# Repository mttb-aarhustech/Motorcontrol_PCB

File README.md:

# Motorcontrol_PCB
Motorcontrol PCB AARHUS TECH

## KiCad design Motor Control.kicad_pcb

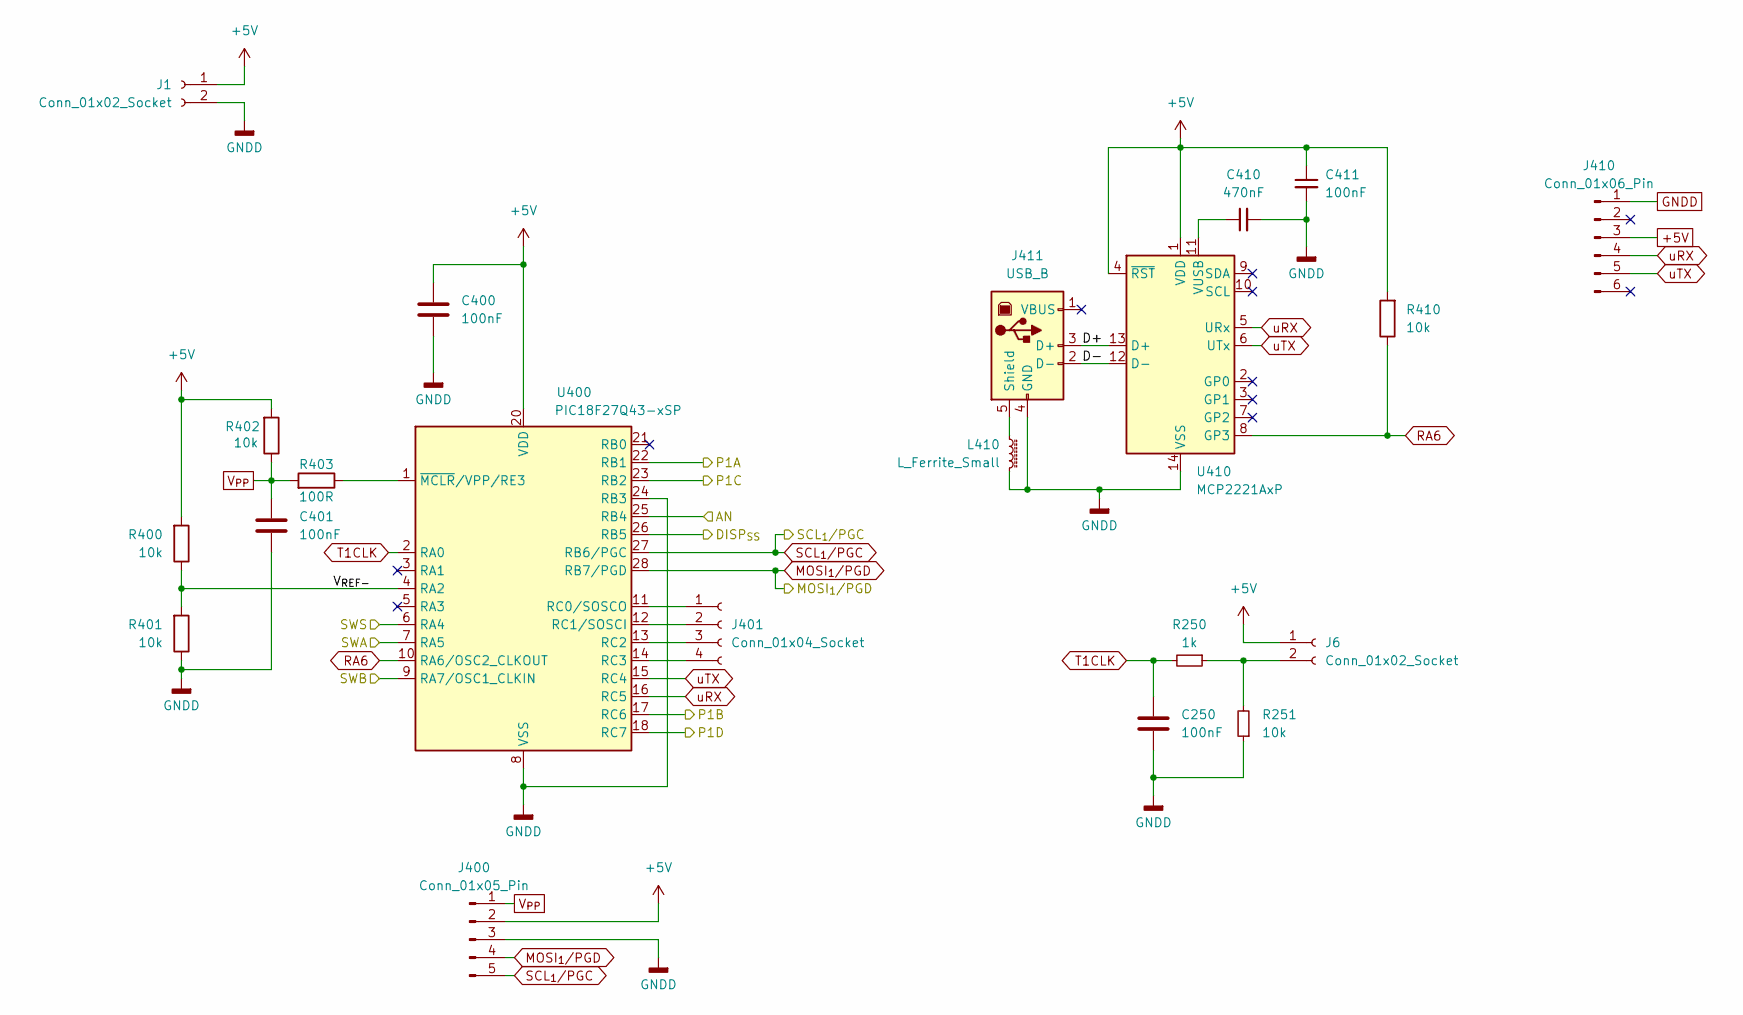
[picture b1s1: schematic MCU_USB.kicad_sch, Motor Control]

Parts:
C250, C400, C401, C411: 100nF; C_Rect_L7.2mm_W2.5mm_P5.00mm_FKS2_FKP2_MKS2_MKP2; Part number 135-8304
C410: 470nF; C_Rect_L7.2mm_W2.5mm_P5.00mm_FKS2_FKP2_MKS2_MKP2; Part number 172-5820
J1, J6: Conn_01x02_Socket; PhoenixContact_MCV_1,5_2-G-5.08_1x02_P5.08mm_Vertical
J400: Conn_01x05_Pin; PinSocket_1x05_P2.54mm_Horizontal; Part number 233-9362
J401: Conn_01x04_Socket; PinSocket_1x04_P2.54mm_Horizontal
J410: Conn_01x06_Pin; PinSocket_1x06_P2.54mm_Vertical
J411: USB_B; USB_B_TE_5787834_Vertical; Part number 1076666
L410: L_Ferrite_Small; R_Axial_DIN0411_L9.9mm_D3.6mm_P12.70mm_Horizontal; Part number 467-3315
R250: 1k; R_Axial_DIN0207_L6.3mm_D2.5mm_P10.16mm_Horizontal; Part number 05.000.0410
R251, R400, R401, R402, R410: 10k; R_Axial_DIN0207_L6.3mm_D2.5mm_P10.16mm_Horizontal; Part number 05.000.0510
R403: 100R; R_Axial_DIN0207_L6.3mm_D2.5mm_P10.16mm_Horizontal; Part number 05.000.0510
U400: PIC18F27Q43-xSP; DIP-28_W7.62mm_Socket_LongPads
U410: MCP2221AxP; DIP-14_W7.62mm_Socket_LongPads; Part number 171-7757

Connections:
+5V: C400.1, C411.1, J1.1, J6.1, J400.2, J410.3, R400.2, R402.2, R410.2, U400.20 (VDD), U410.1 (VDD), U410.4 (~RST); also elsewhere on the board
/Disp & encoder/DISP_{SS}: U400.26 (RB5); also elsewhere on the board
/Disp & encoder/SWA: U400.7 (RA5); also elsewhere on the board
/Disp & encoder/SWB: U400.9 (RA7/OSC1_CLKIN); also elsewhere on the board
/Disp & encoder/SWS: U400.6 (RA4); also elsewhere on the board
/H Bridge/P1A: U400.22 (RB1); also elsewhere on the board
/H Bridge/P1B: U400.17 (RC6); also elsewhere on the board
/H Bridge/P1C: U400.23 (RB2); also elsewhere on the board
/H Bridge/P1D: U400.18 (RC7); also elsewhere on the board
/MCU & USB/AN: U400.25 (RB4); also elsewhere on the board
/MCU & USB/D+: J411.3 (D+), U410.13 (D+)
/MCU & USB/D-: J411.2 (D-), U410.12 (D-)
/MCU & USB/V_{REF-}: R400.1, R401.2, U400.4 (RA2)
GNDD: C250.2, C400.2, C401.2, C410.2, C411.2, J1.2, J400.3, J410.1, J411.4 (GND), L410.2, R251.1, R401.1, U400.8 (VSS), U400.19 (VSS), U400.24 (RB3), U410.14 (VSS); also elsewhere on the board
MOSI_{1}/PGD: J400.4, U400.28 (RB7/PGD); also elsewhere on the board
unnamed: J6.2, R250.1, R251.2
unnamed: J401.1, U400.11 (RC0/SOSCO)
unnamed: J401.2, U400.12 (RC1/SOSCI)
unnamed: J401.3, U400.13 (RC2)
unnamed: J401.4, U400.14 (RC3)
unnamed: J411.5 (Shield), L410.1
unnamed: R403.1, U400.1 (~MCLR/VPP/RE3)
unnamed: C410.1, U410.11 (VUSB)
RA6: R410.1, U400.10 (RA6/OSC2_CLKOUT), U410.8 (GP3)
SCL_{1}/PGC: J400.5, U400.27 (RB6/PGC); also elsewhere on the board
T1CLK: C250.1, R250.2, U400.2 (RA0)
V_{PP}: C401.1, J400.1, R402.1, R403.2
uRX: J410.4, U400.16 (RC5), U410.5 (URx)
uTX: J410.5, U400.15 (RC4), U410.6 (UTx)

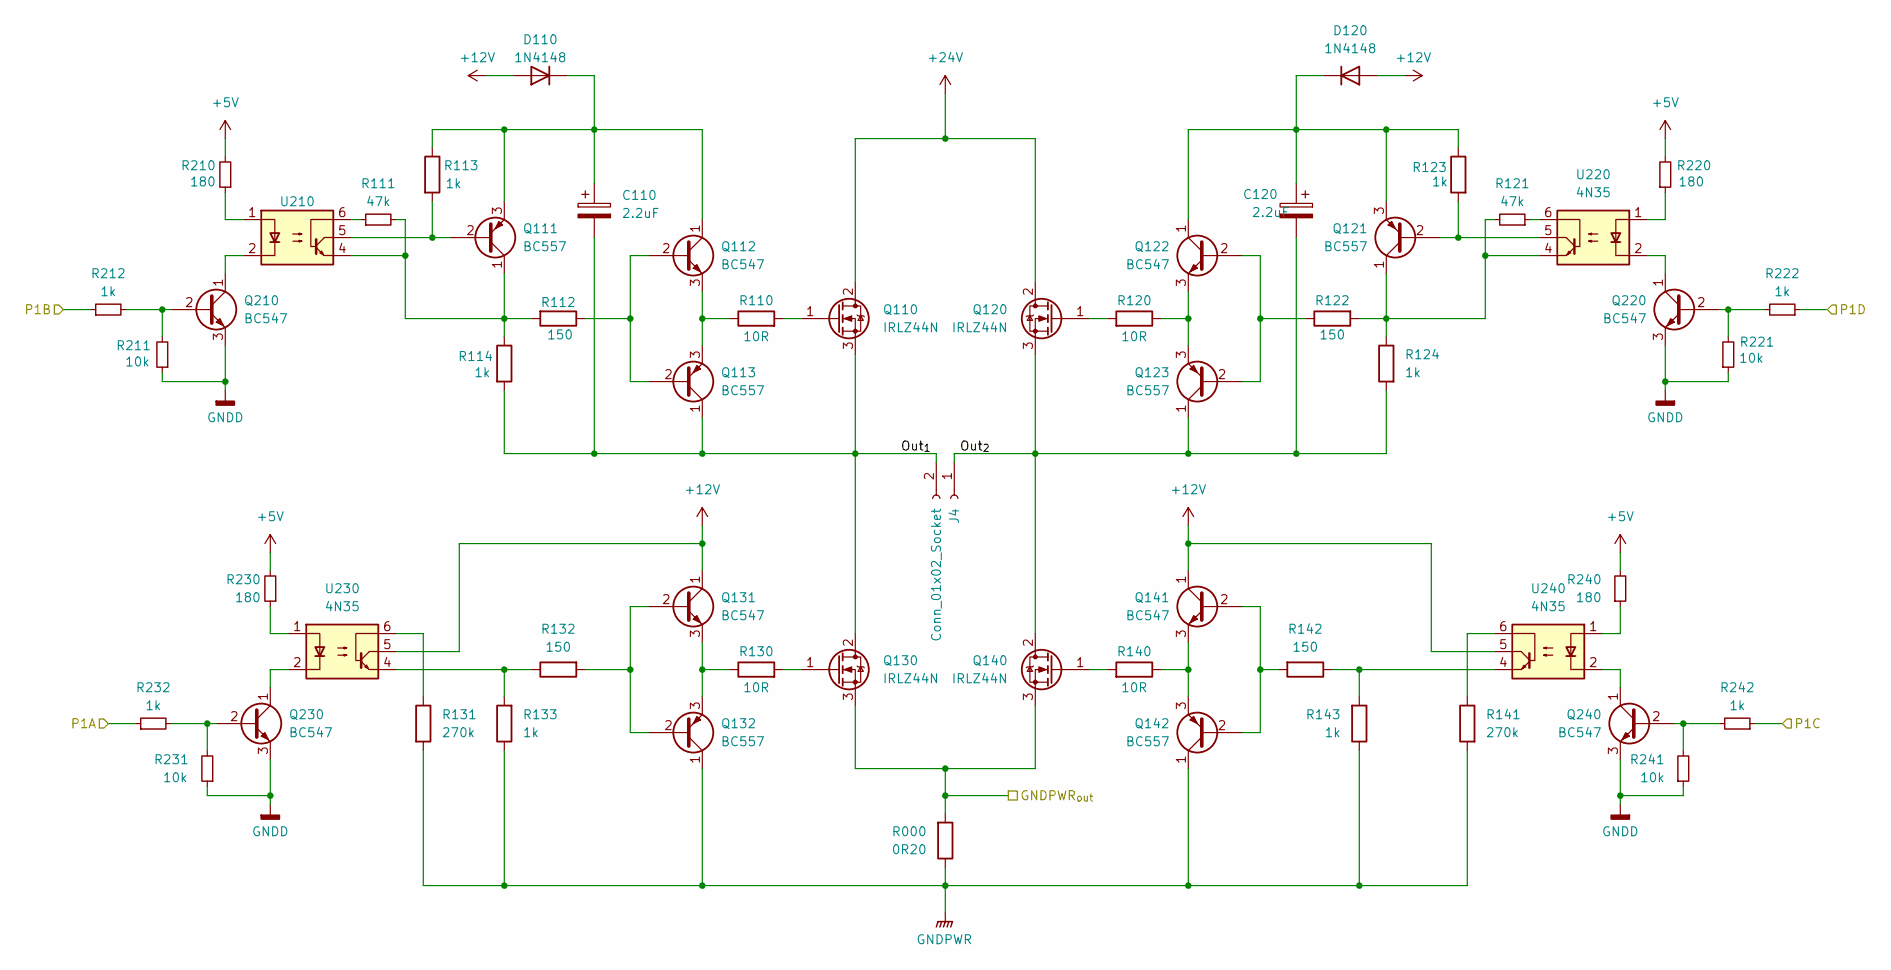
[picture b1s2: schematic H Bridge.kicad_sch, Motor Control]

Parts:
C110, C120: 2.2uF; CP_Radial_D4.0mm_P2.00mm; Part number 8766797
D110, D120: 1N4148; D_DO-35_SOD27_P7.62mm_Horizontal; Part number 00.001.4148
J4: Conn_01x02_Socket; PhoenixContact_MCV_1,5_2-G-5.08_1x02_P5.08mm_Vertical
Q110, Q120, Q130, Q140: IRLZ44N; TO-220-3_Horizontal_TabDown_HoleToCenter; Part number 8651418
Q111, Q113, Q121, Q123, Q132, Q142: BC557; TO-92_Inline_Wide; Part number 01.020.0557
Q112, Q122, Q131, Q141, Q210, Q220, Q230, Q240: BC547; TO-92_Inline_Wide; Part number 01.020.0547
R000: 0R20; R_Axial_DIN0516_L15.5mm_D5.0mm_P20.32mm_Horizontal; Part number 846-9836
R110, R120, R130, R140: 10R; R_Axial_DIN0207_L6.3mm_D2.5mm_P10.16mm_Horizontal; Part number 05.000.0210
R111, R121: 47k; R_Axial_DIN0207_L6.3mm_D2.5mm_P10.16mm_Horizontal; Part number 05.000.0547
R112, R122, R132, R142: 150; R_Axial_DIN0207_L6.3mm_D2.5mm_P10.16mm_Horizontal; Part number 05.000.0315
R113, R114, R123, R124, R133, R143, R212, R222, R232, R242: 1k; R_Axial_DIN0207_L6.3mm_D2.5mm_P10.16mm_Horizontal; Part number 05.000.0410
R131, R141: 270k; R_Axial_DIN0207_L6.3mm_D2.5mm_P10.16mm_Horizontal; Part number 05.000.0627
R210, R220, R230, R240: 180; R_Axial_DIN0207_L6.3mm_D2.5mm_P10.16mm_Horizontal; Part number 05.000.0318
R211, R221, R231, R241: 10k; R_Axial_DIN0207_L6.3mm_D2.5mm_P10.16mm_Horizontal; Part number 05.000.0510
U210, U220, U230, U240: 4N35; DIP-6_W7.62mm_Socket_LongPads; Part number 1021351

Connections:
+5V: R210.2, R220.2, R230.2, R240.2; also elsewhere on the board
+12V: D110.2 (A), D120.2 (A), Q131.1 (C), Q141.1 (C), U230.5, U240.5; also elsewhere on the board
+24V: Q110.2 (D), Q120.2 (D); also elsewhere on the board
/H Bridge/GNDPWR_{out}: Q130.3 (S), Q140.3 (S), R000.2; also elsewhere on the board
/H Bridge/Out_{1}: C110.2, J4.2, Q110.3 (S), Q113.1 (C), Q130.2 (D), R114.2
/H Bridge/Out_{2}: C120.2, J4.1, Q120.3 (S), Q123.1 (C), Q140.2 (D), R124.2
/H Bridge/P1A: R232.1; also elsewhere on the board
/H Bridge/P1B: R212.1; also elsewhere on the board
/H Bridge/P1C: R242.1; also elsewhere on the board
/H Bridge/P1D: R222.1; also elsewhere on the board
GNDD: Q210.3 (E), Q220.3 (E), Q230.3 (E), Q240.3 (E), R211.1, R221.1, R231.1, R241.1; also elsewhere on the board
GNDPWR: Q132.1 (C), Q142.1 (C), R000.1, R131.2, R133.1, R141.2, R143.1; also elsewhere on the board
unnamed: C110.1, D110.1 (K), Q111.3 (E), Q112.1 (C), R113.1
unnamed: C120.1, D120.1 (K), Q121.3 (E), Q122.1 (C), R123.1
unnamed: Q110.1 (G), R110.2
unnamed: Q111.2 (B), R113.2, U210.5
unnamed: Q111.1 (C), R111.2, R112.2, R114.1, U210.4
unnamed: Q112.2 (B), Q113.2 (B), R112.1
unnamed: Q112.3 (E), Q113.3 (E), R110.1
unnamed: Q120.1 (G), R120.2
unnamed: Q121.2 (B), R123.2, U220.5
unnamed: Q121.1 (C), R121.2, R122.2, R124.1, U220.4
unnamed: Q122.2 (B), Q123.2 (B), R122.1
unnamed: Q122.3 (E), Q123.3 (E), R120.1
unnamed: Q130.1 (G), R130.2
unnamed: Q131.2 (B), Q132.2 (B), R132.2
unnamed: Q131.3 (E), Q132.3 (E), R130.1
unnamed: Q140.1 (G), R140.2
unnamed: Q141.2 (B), Q142.2 (B), R142.2
unnamed: Q141.3 (E), Q142.3 (E), R140.1
unnamed: Q210.2 (B), R211.2, R212.2
unnamed: Q210.1 (C), U210.2
unnamed: Q220.2 (B), R221.2, R222.2
unnamed: Q220.1 (C), U220.2
unnamed: Q230.2 (B), R231.2, R232.2
unnamed: Q230.1 (C), U230.2
unnamed: Q240.2 (B), R241.2, R242.2
unnamed: Q240.1 (C), U240.2
unnamed: R111.1, U210.6
unnamed: R121.1, U220.6
unnamed: R131.1, U230.6
unnamed: R132.1, R133.2, U230.4
unnamed: R141.1, U240.6
unnamed: R142.1, R143.2, U240.4
unnamed: R210.1, U210.1
unnamed: R220.1, U220.1
unnamed: R230.1, U230.1
unnamed: R240.1, U240.1

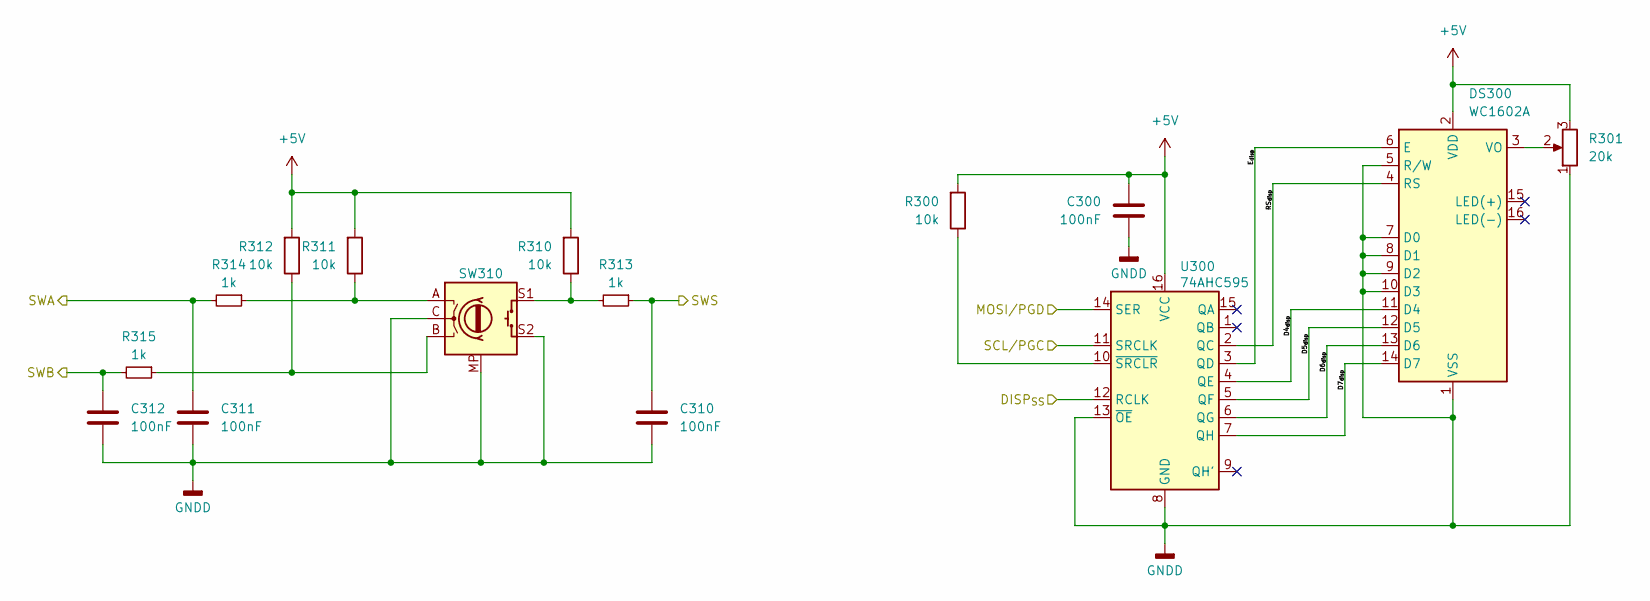
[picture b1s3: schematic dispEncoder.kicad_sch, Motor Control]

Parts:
C300, C310, C311, C312: 100nF; C_Rect_L7.2mm_W2.5mm_P5.00mm_FKS2_FKP2_MKS2_MKP2; Part number 135-8304
DS300: WC1602A; Powertip_PC1602; Part number 1218634
R300, R310, R311, R312: 10k; R_Axial_DIN0207_L6.3mm_D2.5mm_P10.16mm_Horizontal; Part number 05.000.0510
R301: 20k; Potentiometer_Bourns_3339P_Vertical_HandSoldering; Part number 167-3259
R313, R314, R315: 1k; R_Axial_DIN0207_L6.3mm_D2.5mm_P10.16mm_Horizontal; Part number 05.000.0410
SW310: RotaryEncoder_Switch_MP; RotaryEncoder_Bourns-Switch_Vertical_H20mm; Part number 781-6830
U300: 74AHC595; DIP-16_W7.62mm_Socket_LongPads; Part number 100-0763

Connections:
+5V: C300.1, DS300.2 (VDD), R300.2, R301.3, R310.2, R311.2, R312.2, U300.16 (VCC); also elsewhere on the board
/Disp & encoder/D4_{disp}: DS300.11 (D4), U300.4 (QE)
/Disp & encoder/D5_{disp}: DS300.12 (D5), U300.5 (QF)
/Disp & encoder/D6_{disp}: DS300.13 (D6), U300.6 (QG)
/Disp & encoder/D7_{disp}: DS300.14 (D7), U300.7 (QH)
/Disp & encoder/DISP_{SS}: U300.12 (RCLK); also elsewhere on the board
/Disp & encoder/E_{disp}: DS300.6 (E), U300.3 (QD)
/Disp & encoder/RS_{disp}: DS300.4 (RS), U300.2 (QC)
/Disp & encoder/SWA: C311.1, R314.2; also elsewhere on the board
/Disp & encoder/SWB: C312.1, R315.2; also elsewhere on the board
/Disp & encoder/SWS: C310.1, R313.1; also elsewhere on the board
GNDD: C300.2, C310.2, C311.2, C312.2, DS300.1 (VSS), DS300.5 (R/W), DS300.7 (D0), DS300.8 (D1), DS300.9 (D2), DS300.10 (D3), R301.1, SW310.C, SW310.MP, SW310.S2, U300.8 (GND), U300.13 (~OE); also elsewhere on the board
MOSI_{1}/PGD: U300.14 (SER); also elsewhere on the board
unnamed: DS300.3 (VO), R301.2
unnamed: R310.1, R313.2, SW310.S1
unnamed: R311.1, R314.1, SW310.A
unnamed: R312.1, R315.1, SW310.B
unnamed: R300.1, U300.10 (~SRCLR)
SCL_{1}/PGC: U300.11 (SRCLK); also elsewhere on the board

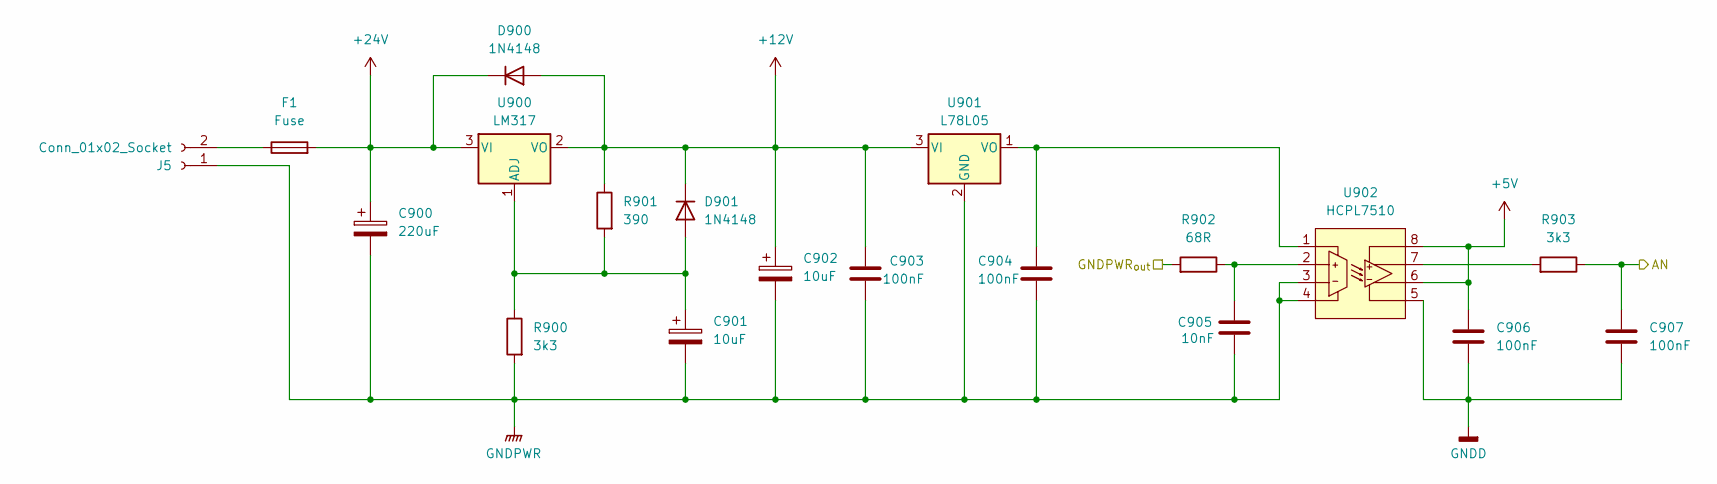
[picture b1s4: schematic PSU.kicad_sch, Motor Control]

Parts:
C900: 220uF; CP_Radial_D8.0mm_P5.00mm; Part number 3254121
C901, C902: 10uF; CP_Radial_D5.0mm_P2.50mm; Part number 2901339
C903, C904, C906, C907: 100nF; C_Rect_L7.2mm_W2.5mm_P5.00mm_FKS2_FKP2_MKS2_MKP2; Part number 135-8304
C905: 10nF; C_Rect_L7.2mm_W2.5mm_P5.00mm_FKS2_FKP2_MKS2_MKP2; Part number 134-5708
D900, D901: 1N4148; D_DO-35_SOD27_P7.62mm_Horizontal; Part number 00.001.4148
F1: Fuse; Fuseholder_Stelvio-kontek_PTF_78_5x20mm
J5: Conn_01x02_Socket; PhoenixContact_MCV_1,5_2-G-5.08_1x02_P5.08mm_Vertical
R900, R903: 3k3; R_Axial_DIN0207_L6.3mm_D2.5mm_P10.16mm_Horizontal; Part number 05.000.0433
R901: 390; R_Axial_DIN0207_L6.3mm_D2.5mm_P10.16mm_Horizontal; Part number 05.000.0339
R902: 68R; R_Axial_DIN0207_L6.3mm_D2.5mm_P10.16mm_Horizontal; Part number 05.000.0268
U900: LM317; TO-220-3_Horizontal_TabDown_HoleToCenter; Part number 168-8786
U901: L78L05; TO-92_Inline_Wide; Part number 885-5423
U902: HCPL7510; DIP-8_W7.62mm_Socket_LongPads; Part number 1085055

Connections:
+5V: C906.1, U902.6 (V_{REF}), U902.8 (V_{DD2}); also elsewhere on the board
+12V: C902.1, C903.1, D900.2 (A), D901.1 (K), R901.1, U900.2 (VO), U901.3 (VI); also elsewhere on the board
+24V: C900.1, D900.1 (K), F1.2, U900.3 (VI); also elsewhere on the board
/H Bridge/GNDPWR_{out}: R902.2; also elsewhere on the board
/MCU & USB/AN: C907.1, R903.1; also elsewhere on the board
GNDD: C906.2, C907.2, U902.5 (GND_{2}); also elsewhere on the board
GNDPWR: C900.2, C901.2, C902.2, C903.2, C904.2, C905.2, J5.1, R900.2, U901.2 (GND), U902.3 (V_{IN-}), U902.4 (GND_{1}); also elsewhere on the board
unnamed: C901.1, D901.2 (A), R900.1, R901.2, U900.1 (ADJ)
unnamed: F1.1, J5.2
unnamed: C904.1, U901.1 (VO), U902.1 (V_{DD1})
unnamed: C905.1, R902.1, U902.2 (V_{IN+})
unnamed: R903.2, U902.7 (V_{OUT})

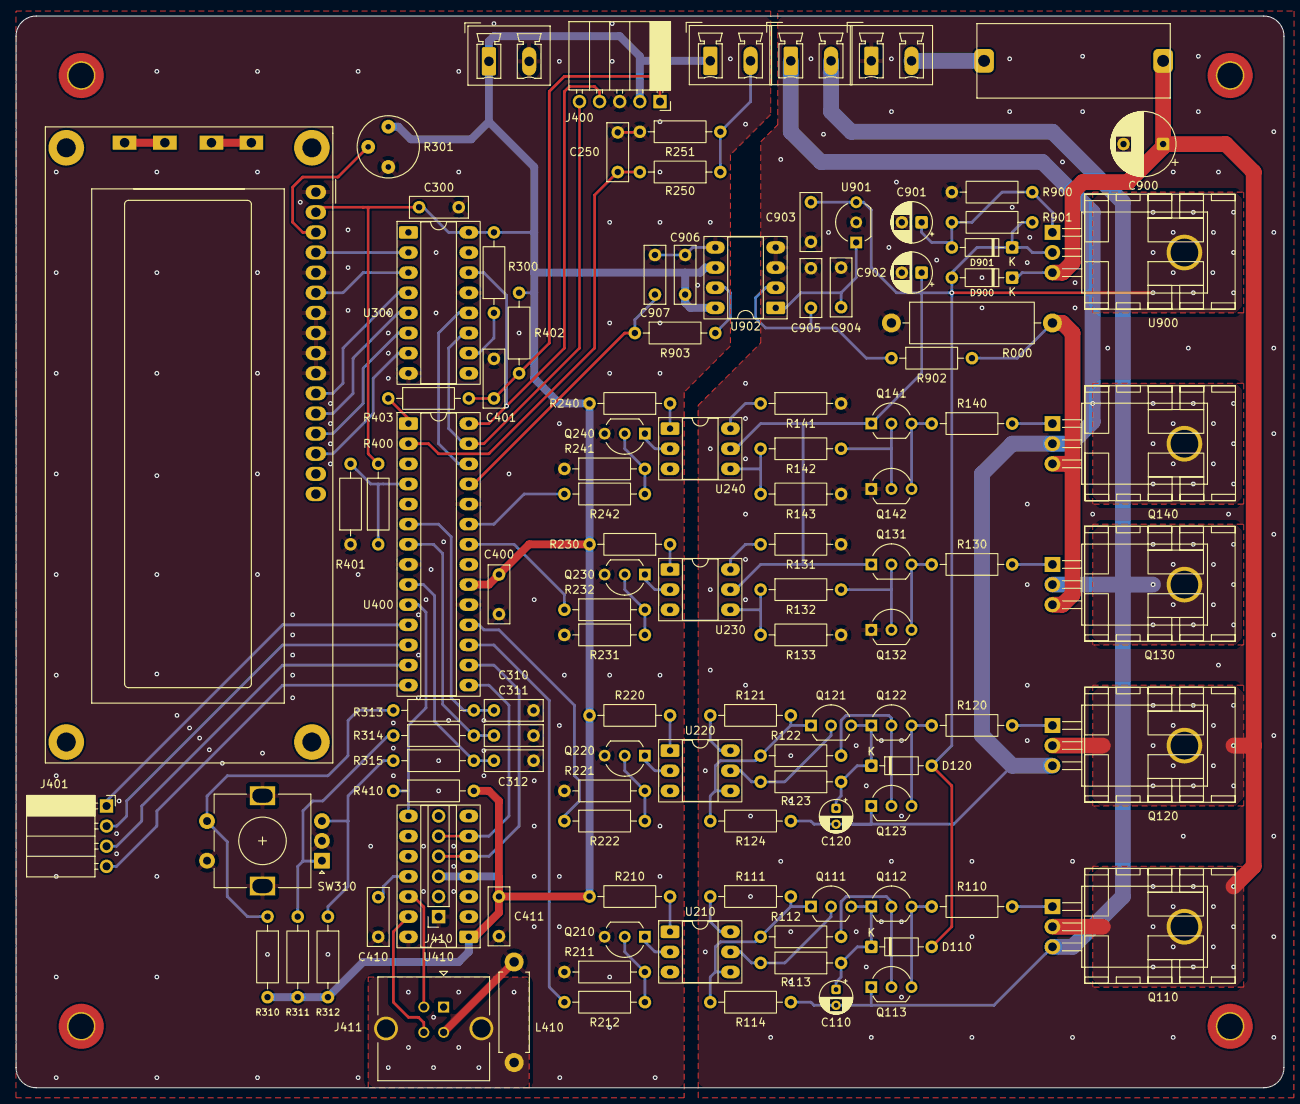
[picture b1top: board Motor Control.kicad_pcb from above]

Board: 2 copper layers, 160.0 x 135.3 mm, 113 parts (0 on the bottom side), 87 nets.

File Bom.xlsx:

Reference | Value | Qty | Supplier | Part number | Column1
J410 | Conn_01x06_Pin | 1 | - | - | 15
D110,D120,D900,D901 | 1N4148 | 4 | Cypax | 00.001.4148 | 60
F1 | Fuse | 1 | Cypax | 18.099.0078.10 | 15
Q111,Q113,Q121,Q123,Q132,Q142 | BC557 | 6 | Cypax | 01.020.0557 | 90
Q112,Q122,Q131,Q141,Q210,Q220,Q230,Q240 | BC547 | 0 | Cypax | 01.020.0547 | 0
R110,R120,R130,R140 | 10R | 4 | Cypax | 05.000.0210 | 60
R111,R121 | 47k | 2 | Cypax | 05.000.0547 | 30
R112,R122,R132,R142 | 150 | 4 | Cypax | 05.000.0315 | 60
R113,R114,R123,R124,R133,R143,R212,R222,R232,R242,R250,R313,R314,R315 | 1k | 14 | Cypax | 05.000.0410 | 210
R131,R141 | 270k | 2 | Cypax | 05.000.0627 | 30
R210,R220,R230,R240 | 180 | 4 | Cypax | 05.000.0318 | 60
R211,R221,R231,R241,R251,R300,R310,R311,R312,R400,R401,R402,R410 | 10k | 13 | Cypax | 05.000.0510 | 195
R403 | 100R | 1 | Cypax | 05.000.0510 | 15
R900,R903 | 3k3 | 2 | Cypax | 05.000.0433 | 30
R901 | 390 | 1 | Cypax | 05.000.0339 | 15
R902 | 68R | 1 | Cypax | 05.000.0268 | 15
C110,C120 | 2.2uF | 2 | Farnell | 8766797 | 30
C900 | 220uF | 1 | Farnell | 3254121 | 15
C901,C902 | 10uF | 2 | Farnell | 2901339 | 30
DS300 | WC1602A | 1 | Farnell | 1218634 | 15
J411 | USB_B | 1 | Farnell | 1076666 | 15
Q110,Q120,Q130,Q140 | IRLZ44N | 4 | Farnell | 8651418 | 60
Q112,Q122,Q131,Q141,Q210,Q220,Q230,Q240 | BC547 | 8 | Farnell | 1574381 | 120
U210,U220,U230,U240 | 4N35 | 4 | Farnell | 1021351 | 60
U400 | PIC18F27Q43-xSP | 0 | Farnell | 3052751 | 0
U410 | MCP2221AxP | 1 | Farnell | 2678459 | 15
U902 | HCPL7510 | 1 | Farnell | 1085055 | 15
C250,C300,C310,C311,C312,C400,C401,C411,C903,C904,C906,C907 | 100nF | ~12 | RS | 135-8304 | 0
C410 | 470nF | 1 | RS | 172-5820 | 15
C905 | 10nF | 1 | RS | 134-5708 | 15
J1,J4,J5,J6 | Conn_01x02_Socket | 1 | RS | 252-5139 | 15
J400 | Conn_01x05_Socket | 1 | RS | 233-9362 | 15
J401 | Conn_01x04_Socket | 1 | RS | 233-9354 | 15
L410 | Ferrite_Small | 1 | RS | 467-3315 | 15
R000 | 0R20 | 1 | RS | 846-9836 | 15
R301 | 20k | 1 | RS | 167-3259 | 15
SW310 | RotaryEncoder_Switch_MP | 1 | RS | 781-6830 | 15
U300 | 74AHC595 | 1 | RS | 100-0763 | 15
U400 | PIC18F27Q43-xSP | 1 | RS | 236-8940 | 15
U410 | MCP2221AxP | 0 | RS | 171-7757 | 0
U900 | LM317 | 1 | RS | 168-8786 | 15
U901 | L78L05 | 1 | RS | 885-5423 | 15
 | Conn_01x02_Plug | 2 | RS | 252-5148 | 30
 | Conn_01x04_Plug | 1 | RS | 252-5150 | 15
 | Conn_01x06_Socket | 1 | RS | 252-5144 | 15
 | Dil socket 28 pin | 1 | RS | 183-1570 | 15
 | Dil socket 16 pin | 1 | RS | 183-1561 | 15
 | Dil socket 14 pin | 1 | RS | 183-1562 | 15
 | Dil socket 8 pin | 1 | RS | 183-1560 | 15
 | Dil socket 6 pin | 4 | RS | 702-0657 | 60

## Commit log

2025-07-03 Initial Project
2025-07-03 H bridge sch. and pcb blocks done
    H bridge schematic done
    H bridge PCB done
    minor silkscreen correction needed
2025-07-04 Placement H bridge & PSU
2025-07-09 Update 090725
    New footprints added
    Schematic made into sub schematics
    PCB needs work
    Component references need to be sorted for the most part
2025-07-12 Almost done
    Schematic done
    PCB missing ground planes
    Need Coopilot review
2025-07-12 Few changes made
2025-07-13 V 1.0 fabrication output
    V 1.0 ready for fabrication
2025-07-17 V 1.0.1
    Stiched vias under TO 220
2025-07-28 Small update 1.0.1
2025-07-28 Partnumbers
2025-11-24 V 2.0
2025-12-16 2.0
    Version 2.0 final
2026-02-17 README.pdf added
